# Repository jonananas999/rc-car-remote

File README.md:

# rc-car-remote
My RC car remote control PCB design and future devolopment

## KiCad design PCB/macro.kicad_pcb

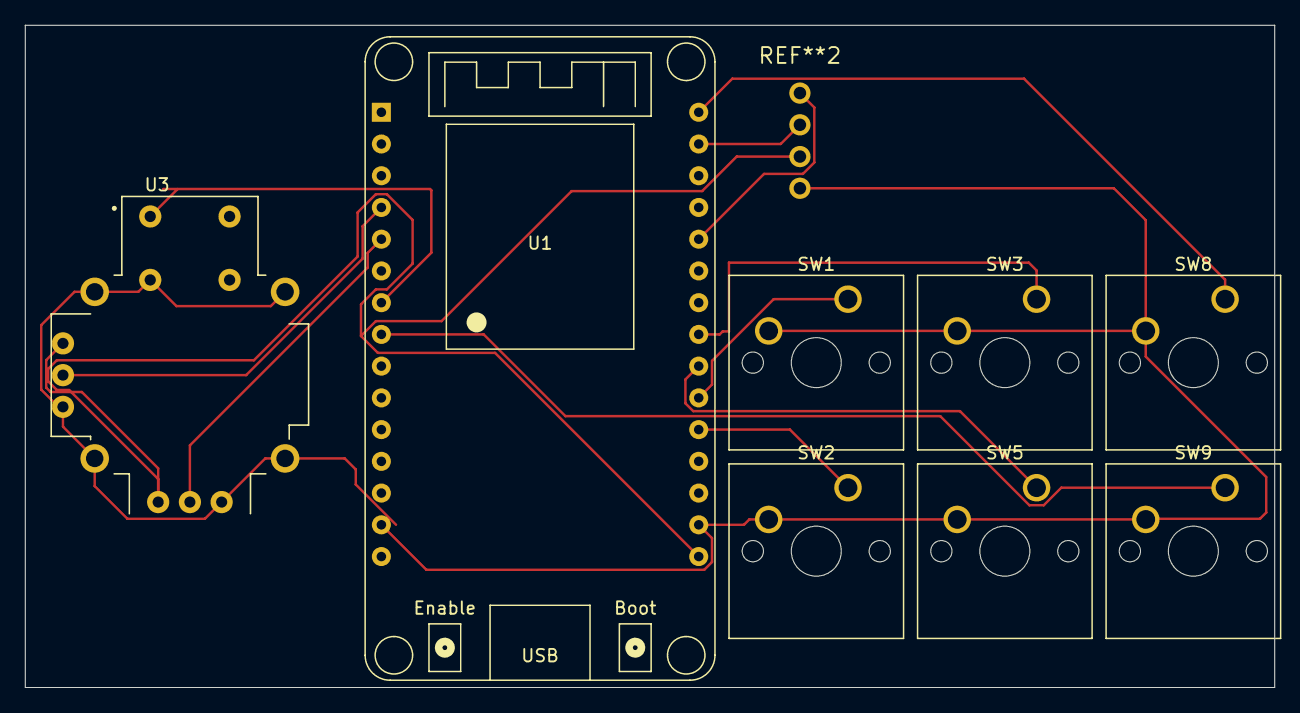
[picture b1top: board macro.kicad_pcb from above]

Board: 2 copper layers, 100.0 x 53.0 mm, 8 parts (0 on the bottom side), 11 nets.

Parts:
SW1, SW2, SW3, SW5, SW8, SW9: SW_Push; SW_Cherry_MX_1.00u_PCB
U1: ESP32_DevKit_V1_DOIT; esp32_devkit_v1_doit
U3: COM-09032; XDCR_COM-09032

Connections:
GND: SW1.2, SW2.2, SW3.2, SW5.2, SW8.2, SW9.2, U1.14 (GND), U1.17 (GND), U3.B2A (SEL-), U3.H3 (H-), U3.S1 (SHIELD), U3.S2 (SHIELD), U3.S3 (SHIELD), U3.S4 (SHIELD), U3.V3 (V-)
unnamed: U1.16 (3V3), U3.H1 (H+), U3.V1 (V+)
unnamed: SW2.1, U1.20 (IO4)
unnamed: SW3.1, U1.23 (IO5)
unnamed: SW1.1, U1.21 (IO16)
unnamed: SW5.1, U1.22 (IO17)
unnamed: SW8.1, U1.30 (IO23)
unnamed: SW9.1, U1.8 (IO25)
unnamed: U1.7 (IO33), U3.B1A (SEL+)
unnamed: U1.4 (IO34), U3.V2 (V)
unnamed: U1.5 (IO35), U3.H2 (H)

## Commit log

2026-03-11 Rename macro.kicad_pro to PCB/macro.kicad_pro
